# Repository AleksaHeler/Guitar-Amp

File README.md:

# Guitar-Amp

Making a solid state combo guitar amp from scratch, based on Marshall MG10 with some custom modifications.

I'm designing my own schematic and PCB, and making the wooden speaker cabinet.

## Resources

...

## Schematic

...

## PCB

...

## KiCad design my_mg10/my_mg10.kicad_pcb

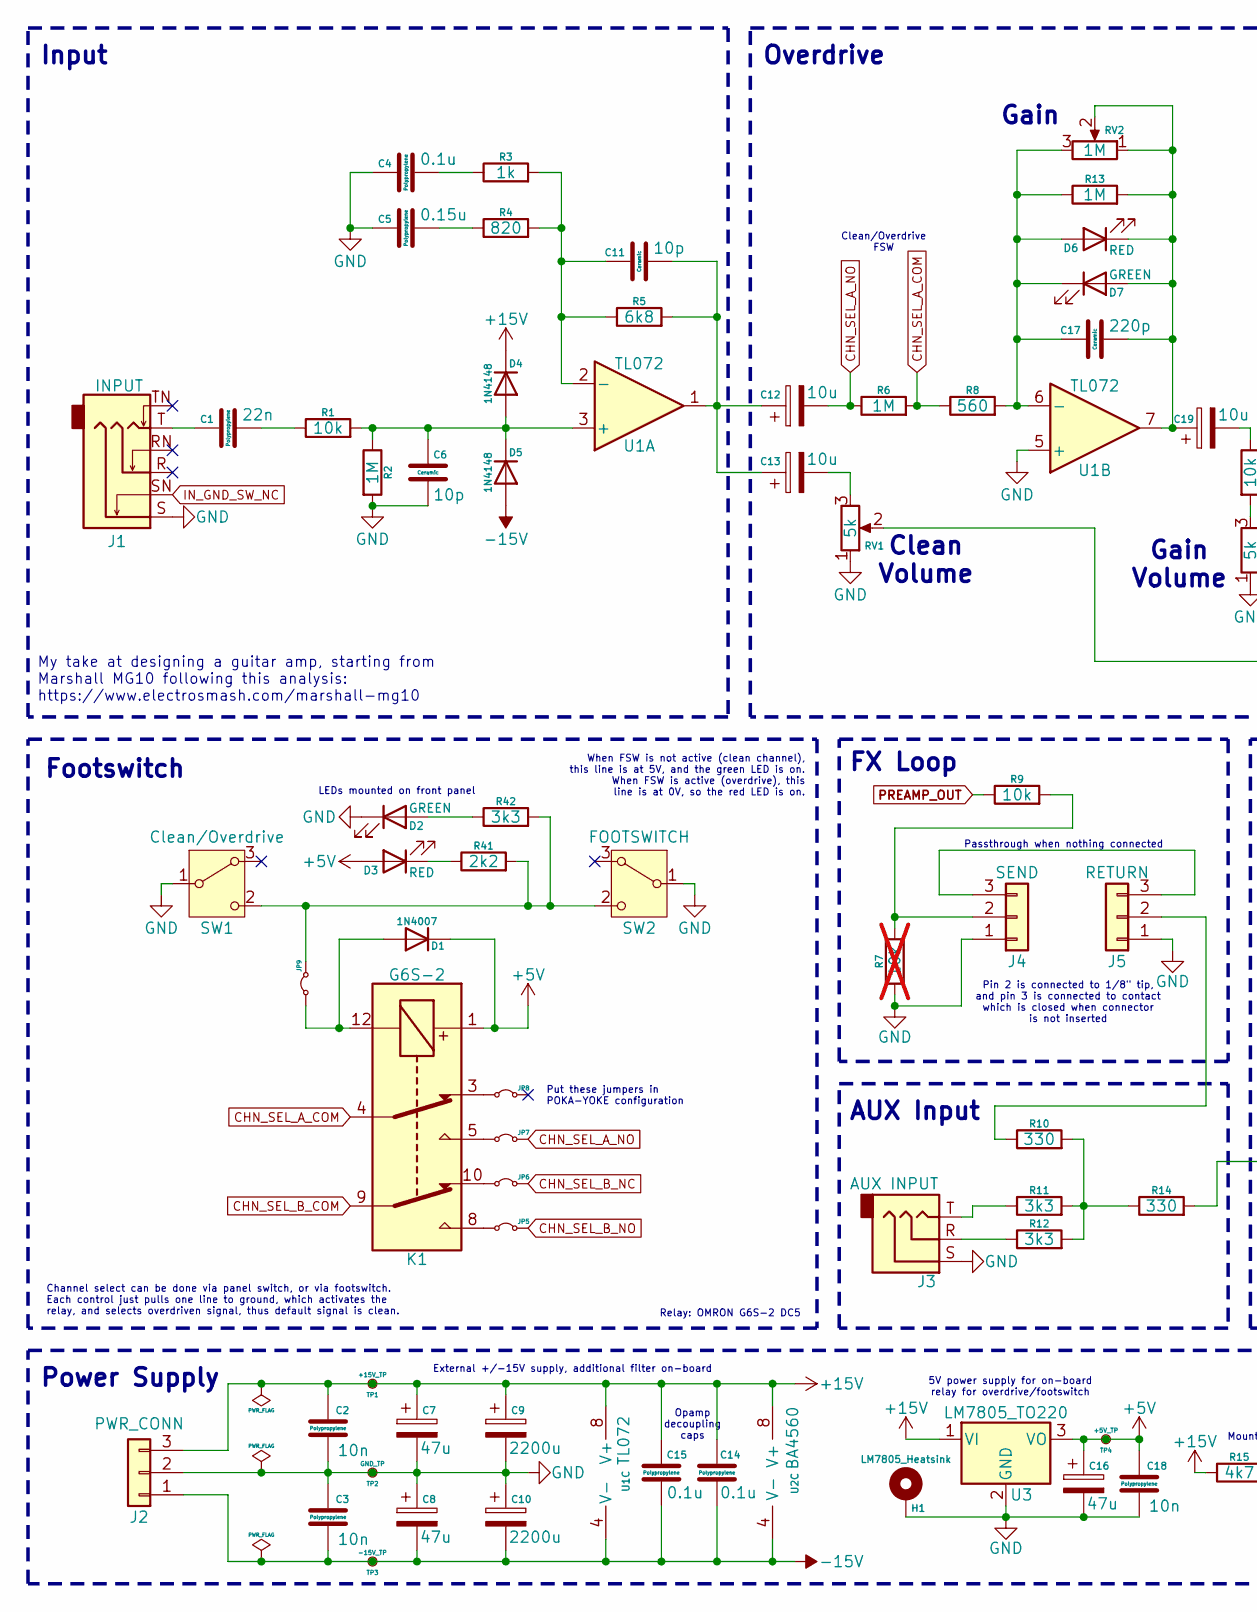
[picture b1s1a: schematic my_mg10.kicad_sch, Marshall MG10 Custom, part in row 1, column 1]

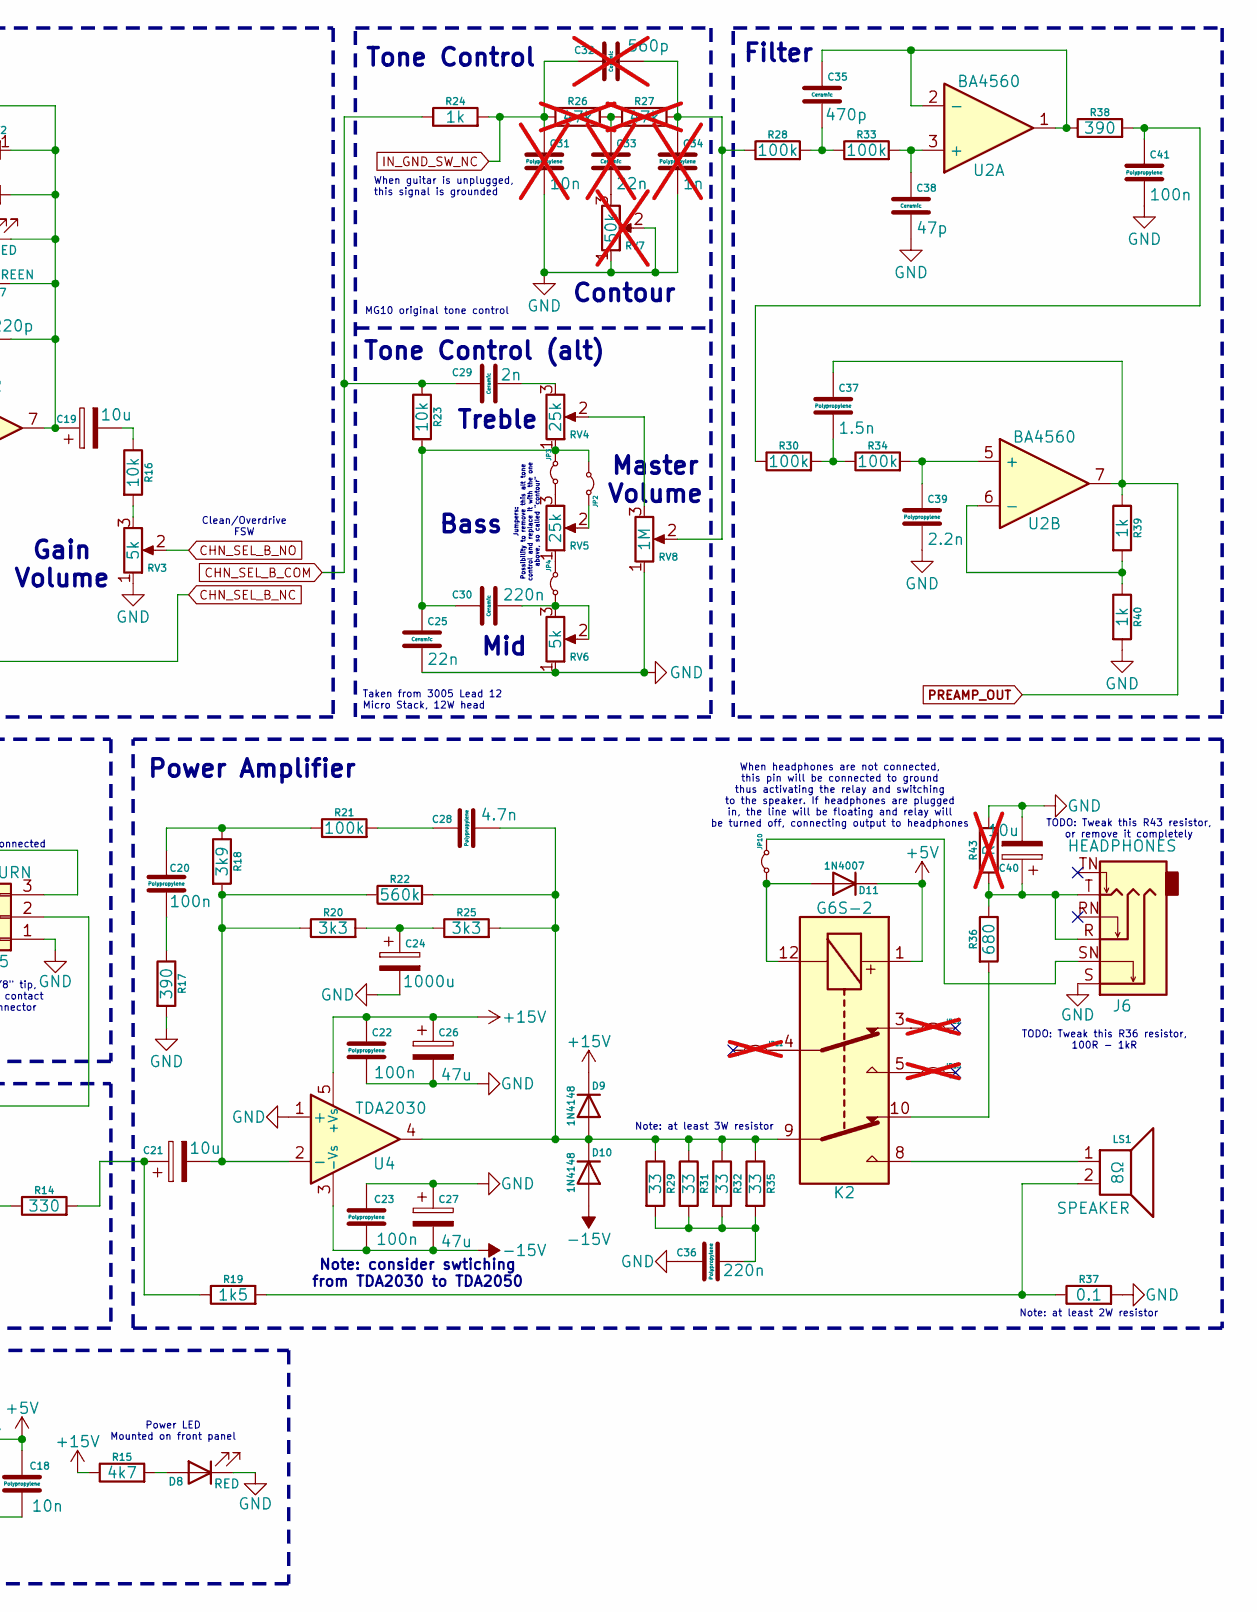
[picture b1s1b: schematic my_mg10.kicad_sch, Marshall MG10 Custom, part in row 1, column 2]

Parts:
C1: 22n; C_Rect_L11.5mm_W5.1mm_P10.00mm_MKT
C2, C3, C18: 10n; C_Rect_L11.5mm_W5.1mm_P10.00mm_MKT
C4, C14, C15: 0.1u; C_Rect_L11.5mm_W5.1mm_P10.00mm_MKT
C5: 0.15u; C_Rect_L11.5mm_W5.1mm_P10.00mm_MKT
C6, C11: 10p; C_Disc_D5.0mm_W2.5mm_P5.00mm
C7, C8, C16, C26, C27: 47u; CP_Radial_D6.3mm_P2.50mm
C9, C10: 2200u; CP_Radial_D13.0mm_P5.00mm
C12, C13, C19, C21, C40: 10u; CP_Radial_D5.0mm_P2.00mm
C17: 220p; C_Disc_D5.0mm_W2.5mm_P5.00mm
C20, C22, C23, C41: 100n; C_Rect_L11.5mm_W5.1mm_P10.00mm_MKT
C24: 1000u; CP_Radial_D10.0mm_P5.00mm
C25: 22n; C_Disc_D5.0mm_W2.5mm_P5.00mm
C28: 4.7n; C_Rect_L11.5mm_W5.1mm_P10.00mm_MKT
C29: 2n; C_Disc_D5.0mm_W2.5mm_P5.00mm
C30: 220n; C_Disc_D5.0mm_W2.5mm_P5.00mm
C31: 10n; C_Rect_L11.5mm_W5.1mm_P10.00mm_MKT; not fitted
C32: 560p; C_Disc_D5.0mm_W2.5mm_P5.00mm; not fitted
C33: 22n; C_Disc_D5.0mm_W2.5mm_P5.00mm; not fitted
C34: 1n; C_Rect_L11.5mm_W5.1mm_P10.00mm_MKT; not fitted
C35: 470p; C_Disc_D5.0mm_W2.5mm_P5.00mm
C36: 220n; C_Rect_L11.5mm_W5.1mm_P10.00mm_MKT
C37: 1.5n; C_Rect_L11.5mm_W5.1mm_P10.00mm_MKT
C38: 47p; C_Disc_D5.0mm_W2.5mm_P5.00mm
C39: 2.2n; C_Rect_L11.5mm_W5.1mm_P10.00mm_MKT
D1, D11: 1N4007; D_DO-41_SOD81_P10.16mm_Horizontal
D2: GREEN; LED_D5.0mm_Horizontal_O6.35mm_Z3.0mm
D3, D8: RED; LED_D5.0mm_Horizontal_O6.35mm_Z3.0mm
D4, D5, D9, D10: 1N4148; D_DO-35_SOD27_P7.62mm_Horizontal
D6: RED; LED_D5.0mm
D7: GREEN; LED_D5.0mm
H1: LM7805_Heatsink; MountingHole_2.5mm_Pad_Via
J1: INPUT; Jack_6.35mm_Neutrik_NMJ6HFD2_Horizontal
J2: PWR_CONN; JST_XH_B3B-XH-A_1x03_P2.50mm_Vertical
J3: AUX INPUT; Jack_3.5mm_CUI_SJ1-3525N_Horizontal
J4: SEND; JST_XH_B3B-XH-A_1x03_P2.50mm_Vertical
J5: RETURN; JST_XH_B3B-XH-A_1x03_P2.50mm_Vertical
J6: HEADPHONES; Jack_6.35mm_Neutrik_NMJ6HFD2_Horizontal
JP2, JP3, JP4: SolderJumper-2_P1.3mm_Bridged_RoundedPad1.0x1.5mm
JP5, JP6, JP7, JP8, JP9, JP10: TestPoint_2Pads_Pitch2.54mm_Drill0.8mm
JP11, JP12, JP13: TestPoint_2Pads_Pitch2.54mm_Drill0.8mm; not fitted
K1, K2: G6S-2; Relay_DPDT_Omron_G6S-2
LS1: SPEAKER; JST_XH_B2B-XH-A_1x02_P2.50mm_Vertical
R1, R9, R16, R23: 10k; R_Axial_DIN0207_L6.3mm_D2.5mm_P7.62mm_Horizontal
R2, R6, R13: 1M; R_Axial_DIN0207_L6.3mm_D2.5mm_P7.62mm_Horizontal
R3, R24, R39, R40: 1k; R_Axial_DIN0207_L6.3mm_D2.5mm_P7.62mm_Horizontal
R4: 820; R_Axial_DIN0207_L6.3mm_D2.5mm_P7.62mm_Horizontal
R5: 6k8; R_Axial_DIN0207_L6.3mm_D2.5mm_P7.62mm_Horizontal
R7: 10k; R_Axial_DIN0207_L6.3mm_D2.5mm_P7.62mm_Horizontal; not fitted
R8: 560; R_Axial_DIN0207_L6.3mm_D2.5mm_P7.62mm_Horizontal
R10, R14: 330; R_Axial_DIN0207_L6.3mm_D2.5mm_P7.62mm_Horizontal
R11, R12, R20, R25, R42: 3k3; R_Axial_DIN0207_L6.3mm_D2.5mm_P7.62mm_Horizontal
R15: 4k7; R_Axial_DIN0207_L6.3mm_D2.5mm_P7.62mm_Horizontal
R17, R38: 390; R_Axial_DIN0207_L6.3mm_D2.5mm_P7.62mm_Horizontal
R18: 3k9; R_Axial_DIN0207_L6.3mm_D2.5mm_P7.62mm_Horizontal
R19: 1k5; R_Axial_DIN0207_L6.3mm_D2.5mm_P7.62mm_Horizontal
R21, R28, R30, R33, R34: 100k; R_Axial_DIN0207_L6.3mm_D2.5mm_P7.62mm_Horizontal
R22: 560k; R_Axial_DIN0207_L6.3mm_D2.5mm_P7.62mm_Horizontal
R26, R27: 47k; R_Axial_DIN0207_L6.3mm_D2.5mm_P7.62mm_Horizontal; not fitted
R29, R31, R32, R35: 33; R_Axial_DIN0414_L11.9mm_D4.5mm_P15.24mm_Horizontal
R36: 680; R_Axial_DIN0207_L6.3mm_D2.5mm_P7.62mm_Horizontal
R37: 0.1; R_Axial_DIN0617_L17.0mm_D6.0mm_P20.32mm_Horizontal
R41: 2k2; R_Axial_DIN0207_L6.3mm_D2.5mm_P7.62mm_Horizontal
R43: R; R_Axial_DIN0207_L6.3mm_D2.5mm_P7.62mm_Horizontal; not fitted
RV1, RV3, RV6: 5k; Potentiometer_Alps_RK163_Single_Horizontal
RV2, RV8: 1M; Potentiometer_Alps_RK163_Single_Horizontal
RV4, RV5: 25k; Potentiometer_Alps_RK163_Single_Horizontal
RV7: 50k; Potentiometer_Alps_RK163_Single_Horizontal; not fitted
SW1: Clean/Overdrive; JST_XH_B3B-XH-A_1x03_P2.50mm_Vertical
SW2: FOOTSWITCH; JST_XH_B3B-XH-A_1x03_P2.50mm_Vertical
TP1: +15V_TP; TestPoint_THTPad_D2.5mm_Drill1.2mm
TP2: GND_TP; TestPoint_THTPad_D2.5mm_Drill1.2mm
TP3: -15V_TP; TestPoint_THTPad_D2.5mm_Drill1.2mm
TP4: +5V_TP; TestPoint_THTPad_D2.5mm_Drill1.2mm
U1: TL072; DIP-8_W7.62mm_Socket
U2: BA4560; DIP-8_W7.62mm_Socket
U3: LM7805_TO220; TO-220-3_Vertical
U4: TDA2030; TO-220-5_P3.4x3.7mm_StaggerOdd_Lead3.8mm_Vertical

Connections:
+5V: C16.1, C18.1, D1.1 (K), D3.2 (A), D11.1 (K), K1.1, K2.1, TP4.1, U3.3 (VO)
+15V: C2.1, C7.1, C9.1, C14.1, C15.1, C22.1, C26.1, D4.1 (K), D9.1 (K), J2.3, R15.1, TP1.1, U1.8 (V+), U2.8 (V+), U3.1 (VI), U4.5 (+Vs)
-15V: C3.2, C8.2, C10.2, C14.2, C15.2, C23.2, C27.2, D5.2 (A), D10.2 (A), J2.1, TP3.1, U1.4 (V-), U2.4 (V-), U4.3 (-Vs)
CHN_SEL_A_COM: K1.4, R6.2, R8.1
CHN_SEL_A_NO: C12.2, JP7.2 (B), R6.1
CHN_SEL_B_COM: C29.1, K1.9, R23.1, R24.1
CHN_SEL_B_NC: JP6.2 (B), RV1.2
CHN_SEL_B_NO: JP5.2 (B), RV3.2
GND: C2.2, C3.1, C4.1, C5.1, C6.2, C7.2, C8.1, C9.2, C10.1, C16.2, C18.2, C22.2, C23.1, C24.2, C25.2, C26.2, C27.1, C31.2, C34.2, C36.1, C38.2, C39.2, C40.2, C41.2, D2.1 (K), D8.1 (K), H1.1, J1.S, J2.2, J3.S, J4.1, J5.1, J6.S, R2.2, R7.1, R17.2, R37.2, R40.2, R43.2, RV1.1, RV3.1, RV6.1, RV7.1, RV7.2, RV8.1, SW1.1 (B), SW2.1 (B), TP2.1, U1.5 (+), U3.2 (GND), U4.1 (+)
IN_GND_SW_NC: C31.1, C32.1, J1.SN, R24.2, R26.1
unnamed: C1.1, J1.T
unnamed: C1.2, R1.1
unnamed: C4.2, R3.1
unnamed: C5.2, R4.1
unnamed: C11.2, C12.1, C13.1, R5.2, U1.1
unnamed: C13.2, RV1.3
unnamed: C19.2, R16.1
unnamed: C20.1, R18.1, R21.1
unnamed: C20.2, R17.1
unnamed: C21.1, R14.2, R19.1
unnamed: C24.1, R20.2, R25.1
unnamed: C28.1, R21.2
unnamed: C29.2, RV4.3
unnamed: C32.2, C34.1, R27.2, R28.1, RV8.2
unnamed: C33.1, R26.2, R27.1
unnamed: C33.2, RV7.3
unnamed: C35.2, R28.2, R33.1
unnamed: C36.2, R29.2, R31.2, R32.2, R35.2
unnamed: C37.2, R30.2, R34.1
unnamed: C40.1, J6.R, J6.T, R36.1, R43.1
unnamed: C41.1, R30.1, R38.2
unnamed: D1.2 (A), JP9.1 (A), K1.12
unnamed: D2.2 (A), R42.1
unnamed: D3.1 (K), R41.1
unnamed: C6.1, D4.2 (A), D5.1 (K), R1.2, R2.1, U1.3 (+)
unnamed: C17.1, D6.2 (A), D7.1 (K), R8.2, R13.1, RV2.3, U1.6 (-)
unnamed: C17.2, C19.1, D6.1 (K), D7.2 (A), R13.2, RV2.1, RV2.2, U1.7
unnamed: D8.2 (A), R15.2
unnamed: C28.2, D9.2 (A), D10.1 (K), K2.9, R22.2, R25.2, R29.1, R31.1, R32.1, R35.1, U4.4
unnamed: D11.2 (A), JP10.1 (A), K2.12
unnamed: J3.R, R12.1
unnamed: J3.T, R11.1
unnamed: J4.2, R7.2, R9.2
unnamed: J4.3, J5.3
unnamed: J5.2, R10.1
unnamed: C25.1, C30.1, JP2.1 (A), JP3.2 (B), R23.2, RV4.1
unnamed: JP2.2 (B), RV5.2
unnamed: JP3.1 (A), RV5.3
unnamed: C30.2, JP4.1 (A), RV6.2, RV6.3
unnamed: JP4.2 (B), RV5.1
unnamed: JP5.1 (A), K1.8
unnamed: JP6.1 (A), K1.10
unnamed: JP7.1 (A), K1.5
unnamed: JP8.1 (A), K1.3
unnamed: JP9.2 (B), R41.2, R42.2, SW1.2 (C), SW2.2 (C)
unnamed: J6.SN, JP10.2 (B)
unnamed: JP11.2 (B), K2.4
unnamed: JP12.1 (A), K2.3
unnamed: JP13.1 (A), K2.5
unnamed: K2.8, LS1.1
unnamed: K2.10, R36.2
unnamed: LS1.2, R19.2, R37.1
unnamed: R10.2, R11.2, R12.2, R14.1
unnamed: R16.2, RV3.3
unnamed: RV4.2, RV8.3
unnamed: C11.1, R3.2, R4.2, R5.1, U1.2 (-)
unnamed: C38.1, R33.2, U2.3 (+)
unnamed: C35.1, R38.1, U2.1, U2.2 (-)
unnamed: C39.1, R34.2, U2.5 (+)
unnamed: R39.2, R40.1, U2.6 (-)
unnamed: C21.2, R18.2, R20.1, R22.1, U4.2 (-)
PREAMP_OUT: C37.1, R9.1, R39.1, U2.7

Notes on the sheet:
Gain
External +/-15V supply, additional filter on-board
Treble
MG10 original tone control
When FSW is not active (clean channel), this line is at 5V, and the green LED is on. When FSW is active (overdrive), this line is at 0V, so the red LED is on.
5V power supply for on-board relay for overdrive/footswitch
Mid
Channel select can be done via panel switch, or via footswitch. Each control just pulls one line to ground, which activates the relay, and selects overdriven signal, thus default signal is clean.
AUX Input
Tone Control (alt)
Power Amplifier
Jumpers: Possibility to remove this alt tone control and replace it with the one above, so called "contour"
Relay: OMRON G6S-2 DC5
TODO: Tweak this R36 resistor, 100R - 1kR
Filter
Taken from 3005 Lead 12 Micro Stack, 12W head
Power Supply
Gain Volume
Opamp decoupling caps
FX Loop
Clean/Overdrive FSW
Passthrough when nothing connected
Master Volume
Footswitch
Bass
Put these jumpers in POKA-YOKE configuration
Input
Note: consider swtiching from TDA2030 to TDA2050
Power LED Mounted on front panel
Overdrive
Clean Volume
Pin 2 is connected to 1/8" tip, and pin 3 is connected to contact which is closed when connector is not inserted
When headphones are not connected, this pin will be connected to ground thus activating the relay and switching to the speaker. If headphones are plugged in, the line will be floating and relay will be turned off, connecting output to headphones
Contour
TODO: Tweak this R43 resistor, or remove it completely
LEDs mounted on front panel
When guitar is unplugged, this signal is grounded
Tone Control
Note: at least 3W resistor
Note: at least 2W resistor

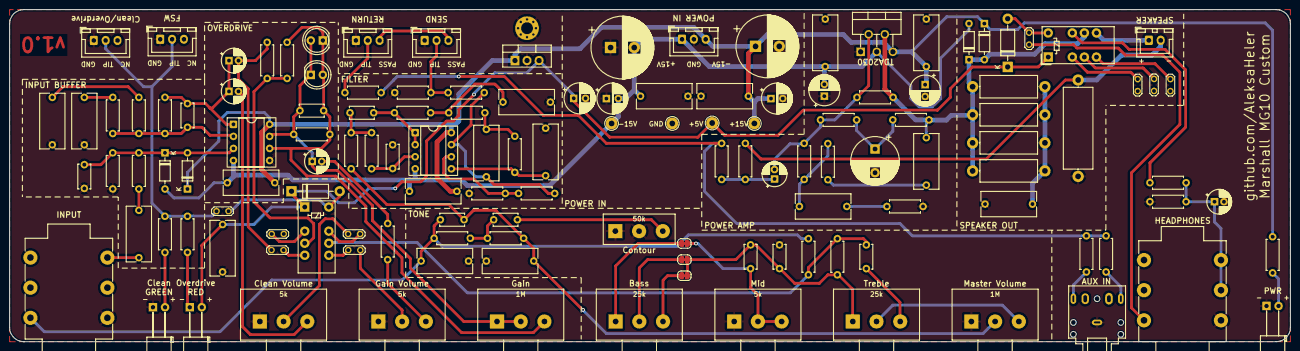
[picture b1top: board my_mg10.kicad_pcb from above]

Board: 2 copper layers, 270.0 x 70.0 mm, 135 parts (0 on the bottom side), 72 nets.

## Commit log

2025-09-01 Minor file tweaks
2025-09-01 Added headphone out switching, added pictures
